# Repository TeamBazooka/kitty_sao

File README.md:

# Kitty Shitty add-on

## BOM
1. [LED](https://www.digikey.com/product-detail/en/osram-opto-semiconductors-inc/LY-T776-R1S2-26-Z/475-1149-1-ND/808919)
2. Resistor, pick one you like
3. 0.1" pin headers can be had places.

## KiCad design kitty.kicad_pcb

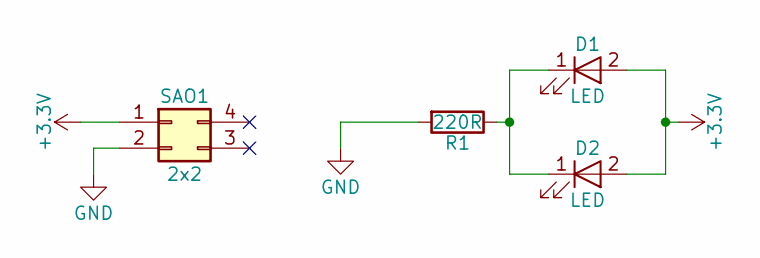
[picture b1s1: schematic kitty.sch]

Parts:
D1, D2: LED
R1: 220R; R_0805
SAO1: 2x2; Pin_Header_Straight_2x02_Pitch2.54mm

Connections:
+3V3: D1.2 (A), D2.2 (A), SAO1.1
GND: R1.2, SAO1.2
unnamed: D1.1 (K), D2.1 (K), R1.1

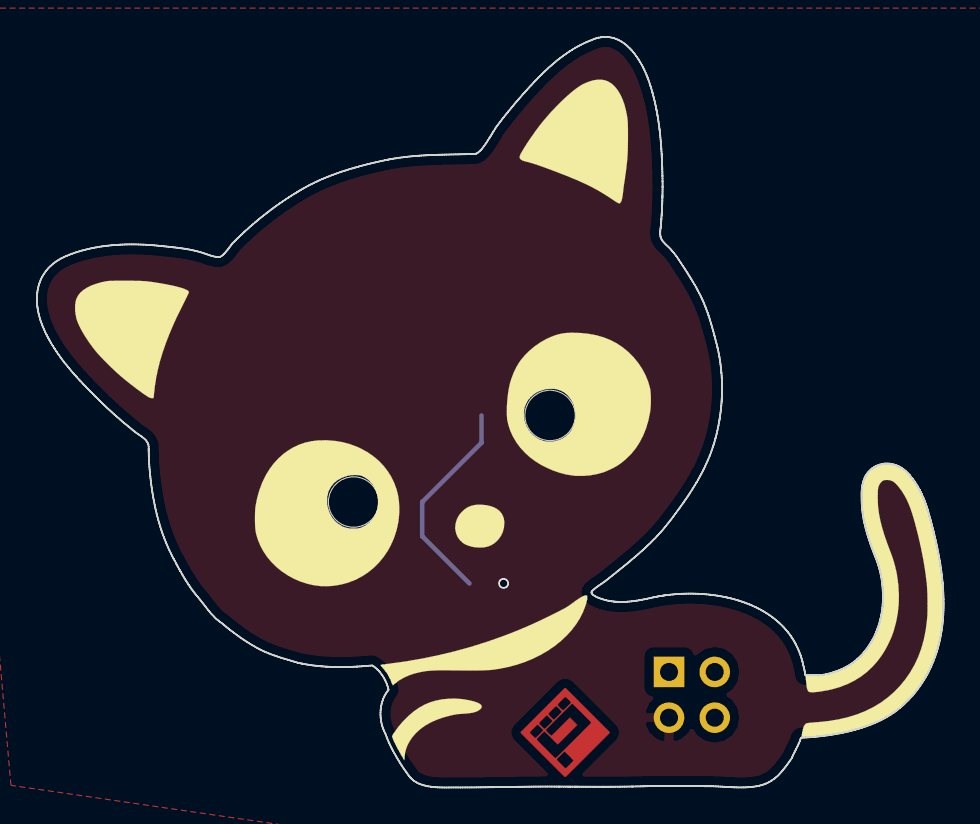
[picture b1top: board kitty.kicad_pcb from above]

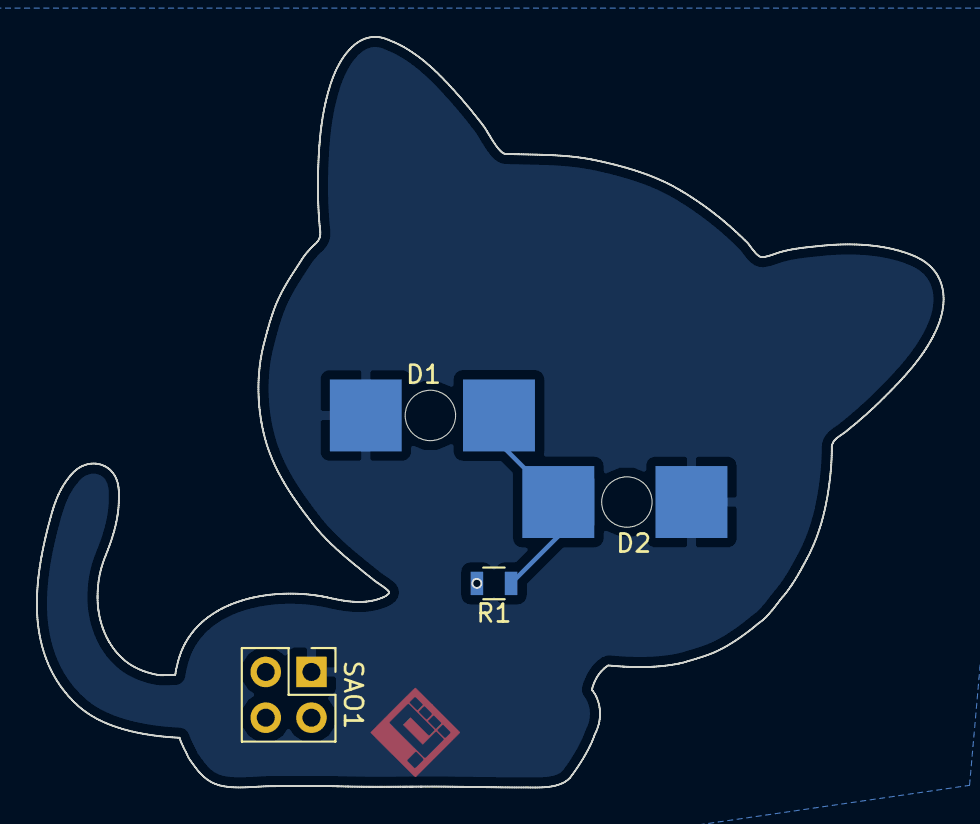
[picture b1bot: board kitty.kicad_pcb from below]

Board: 2 copper layers, 50.4 x 41.7 mm, 4 parts (4 on the bottom side), 3 nets.

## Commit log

2018-07-19 got the kat drawn
2018-07-19 got the cat into kicad
2018-07-19 Update fill colors in cat sag
2018-07-19 Add schematic
2018-07-19 finish layout
2018-07-19 fix SAO header
2018-07-25 Add PCB picture
